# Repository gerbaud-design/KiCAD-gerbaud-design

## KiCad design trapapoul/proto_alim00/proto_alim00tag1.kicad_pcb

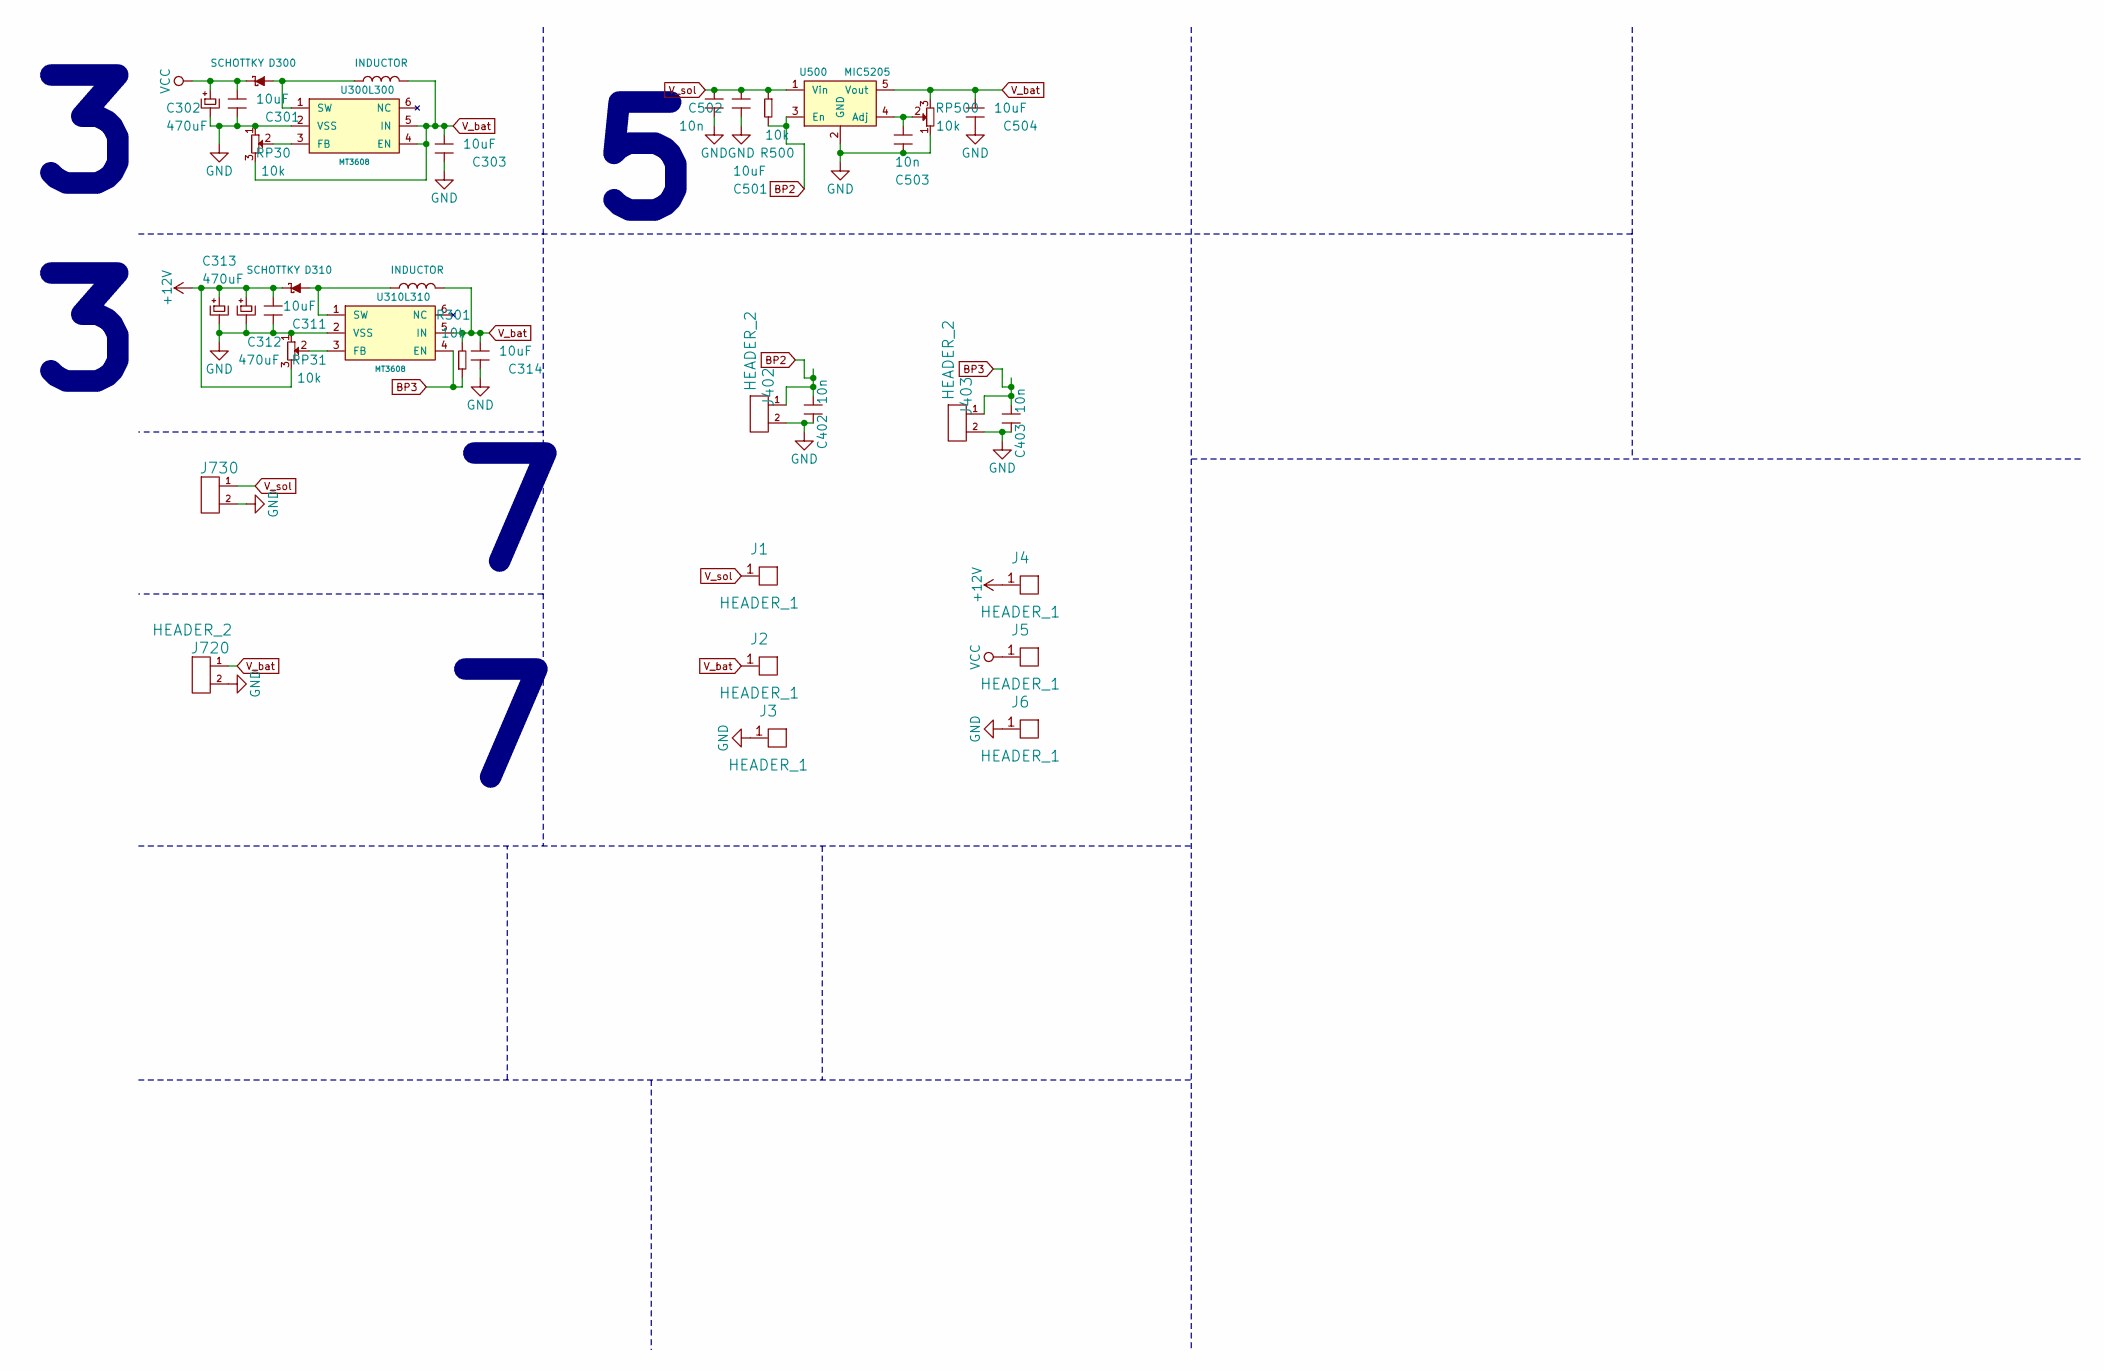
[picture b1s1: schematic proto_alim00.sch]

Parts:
C301, C303, C311, C314, C501, C504: 10uF; C_1206_HandSoldering
C302, C312, C313: 470uF; C_Radial_D8_L11.5_P3.5
C402, C403, C502, C503: 10n; C_1206_HandSoldering
D300, D310: SCHOTTKY; MiniMELF_Handsoldering
J1, J2, J3, J4, J5, J6: HEADER_1; Pin_Header_Straight_1x01
J402, J403, J720, J730: HEADER_2; Pin_Header_Straight_1x02
L300, L310: INDUCTOR; R_1206_HandSoldering
R301, R500: 10k; R_1206_HandSoldering
RP30, RP31, RP500: 10k; Potentiometer_Triwood_RM-065
U300, U310: MT3608; SOT-23-6_Handsoldering
U500: MIC5205; SOT-23-5_Handsoldering

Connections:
+12V: C311.1, C312.1, C313.1, D310.2 (K), J4.1, RP31.3
BP2: C402.1, J402.1, R500.2, U500.3 (En)
BP3: C403.1, J403.1, R301.1, U310.4 (EN)
GND: C301.2, C302.2, C303.2, C311.2, C312.2, C313.2, C314.2, C402.2, C403.2, C501.2, C502.2, C503.2, C504.2, J3.1, J6.1, J402.2, J403.2, J720.2, J730.2, RP30.1, RP31.1, RP500.1, U300.2 (VSS), U310.2 (VSS), U500.2 (GND)
unnamed: C503.1, RP500.2, U500.4 (Adj)
unnamed: D300.1 (A), L300.1, U300.1 (SW)
unnamed: D310.1 (A), L310.1, U310.1 (SW)
unnamed: RP30.2, U300.3 (FB)
unnamed: RP31.2, U310.3 (FB)
VCC: C301.1, C302.1, D300.2 (K), J5.1
V_bat: C303.1, C314.1, C504.1, J2.1, J720.1, L300.2, L310.2, R301.2, RP30.3, RP500.3, U300.4 (EN), U300.5 (IN), U310.5 (IN), U500.5 (Vout)
V_sol: C501.1, C502.1, J1.1, J730.1, R500.1, U500.1 (Vin)

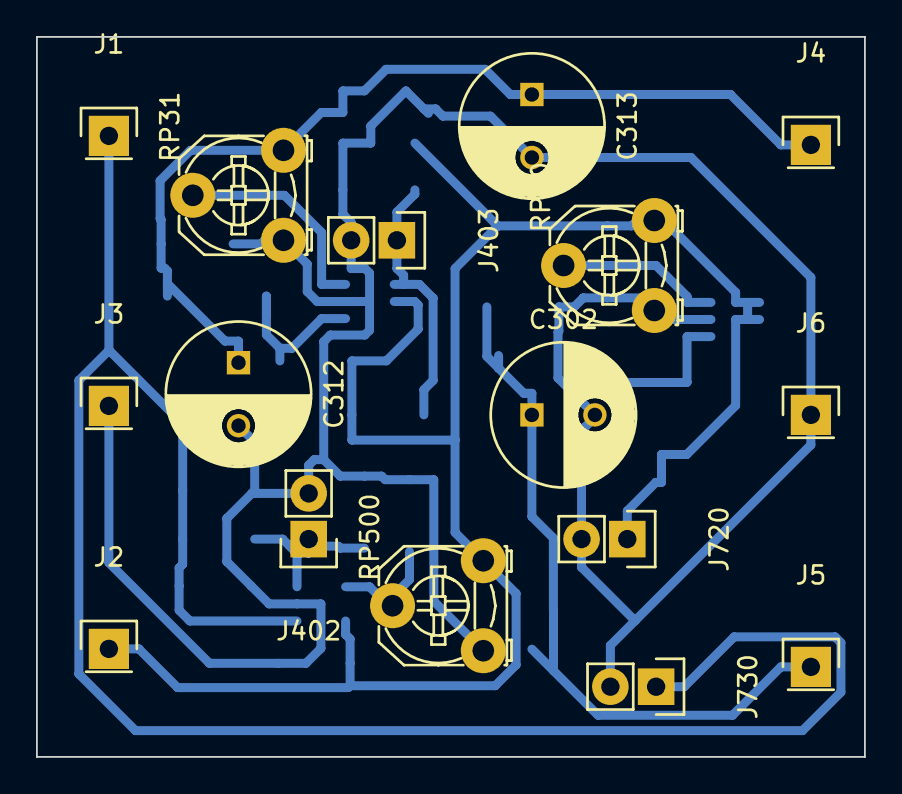
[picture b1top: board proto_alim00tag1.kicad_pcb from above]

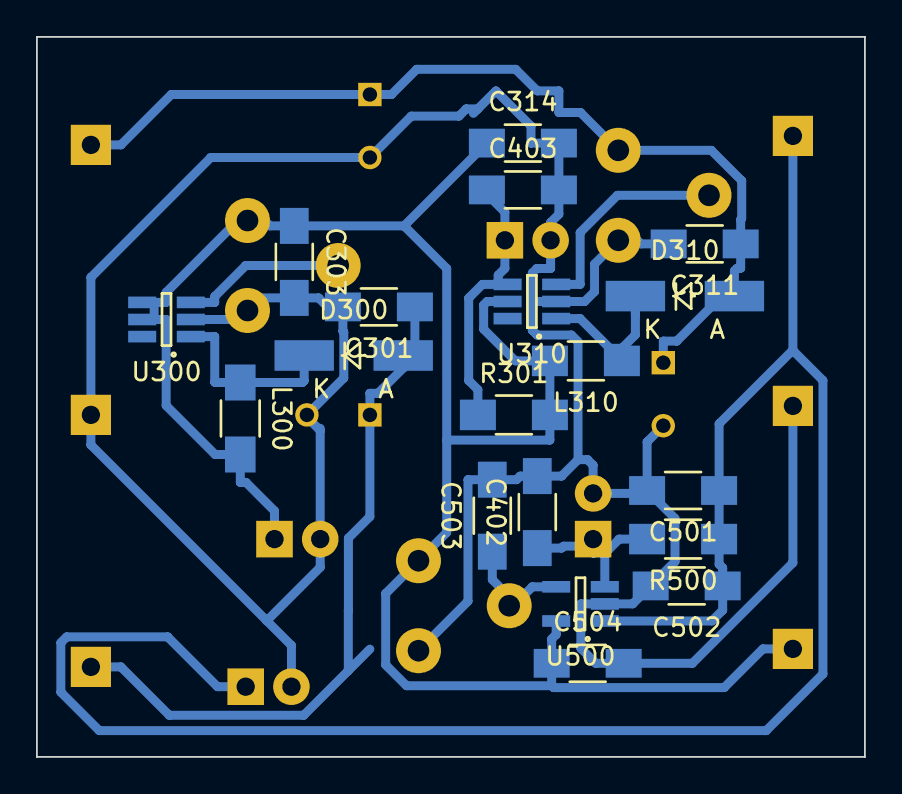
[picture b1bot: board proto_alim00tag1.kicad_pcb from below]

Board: 2 copper layers, 46.0 x 40.0 mm, 35 parts (19 on the bottom side), 12 nets.

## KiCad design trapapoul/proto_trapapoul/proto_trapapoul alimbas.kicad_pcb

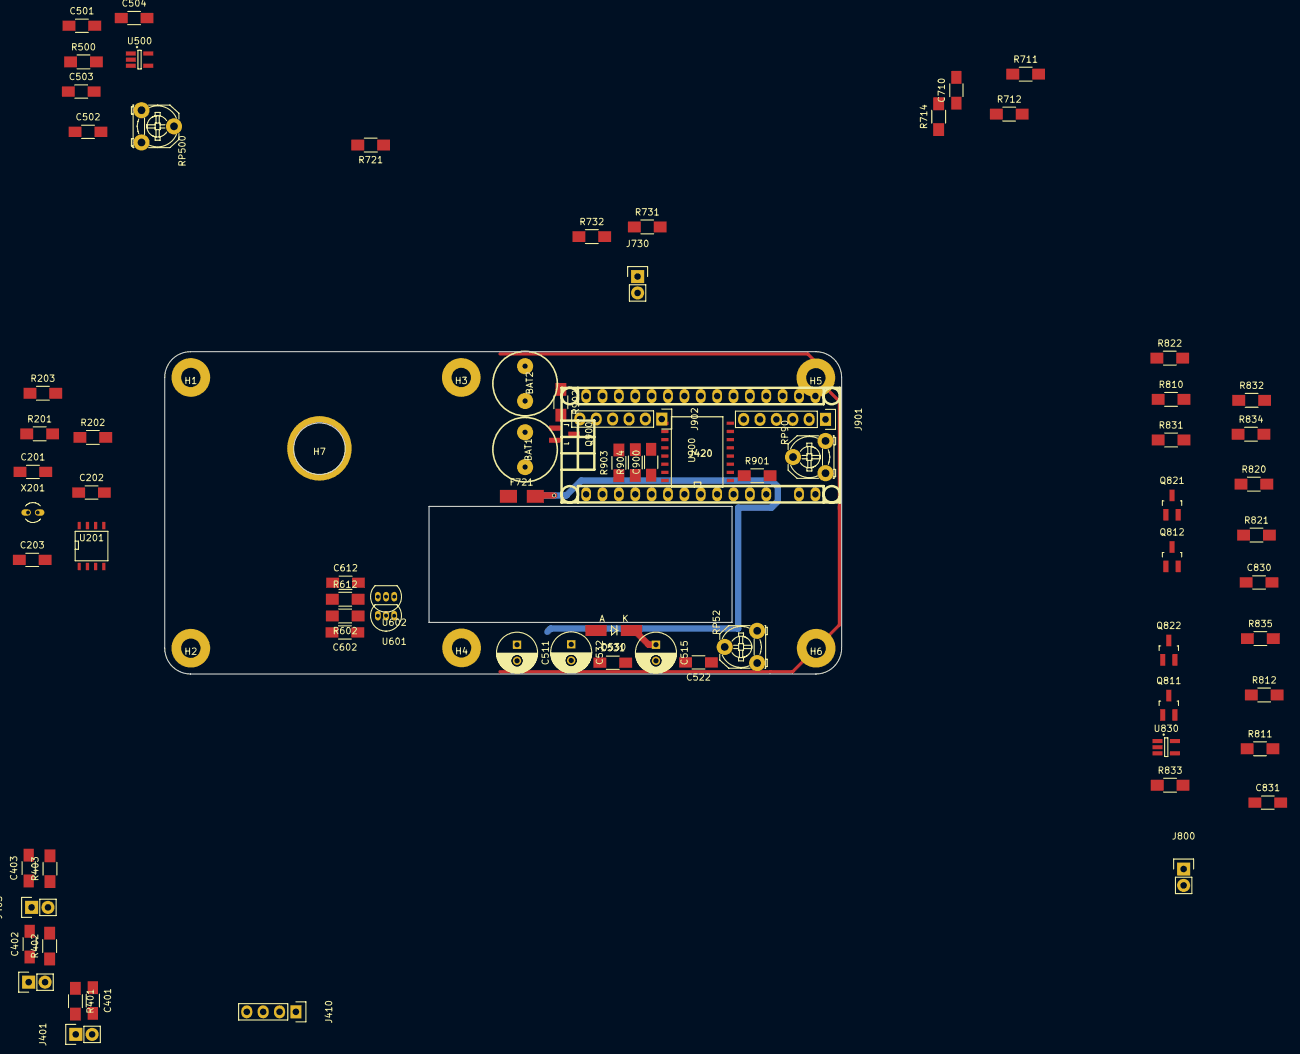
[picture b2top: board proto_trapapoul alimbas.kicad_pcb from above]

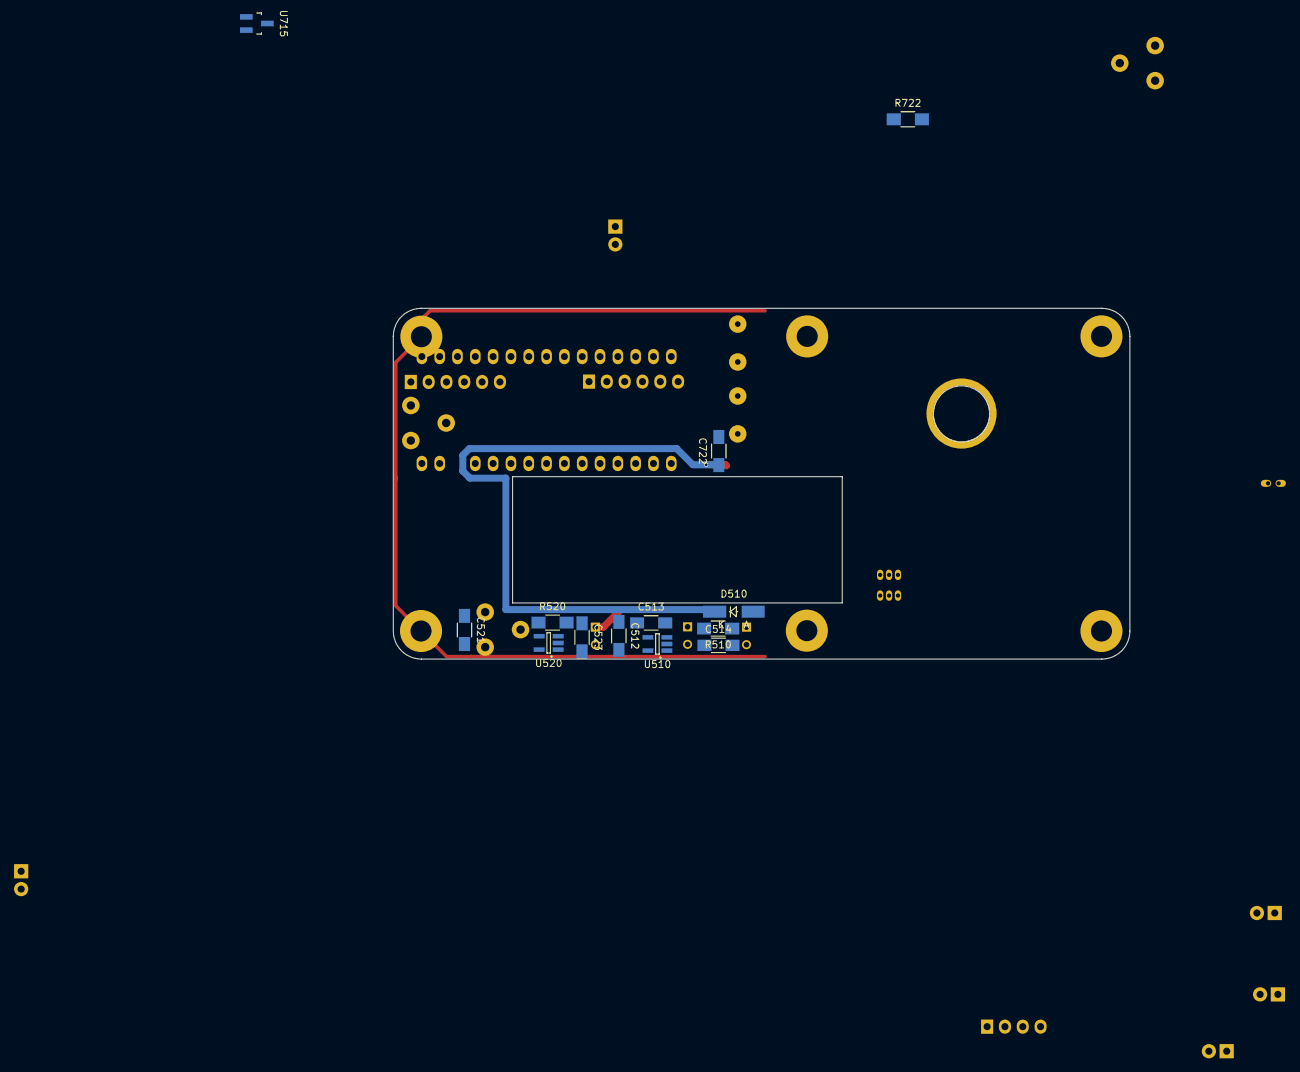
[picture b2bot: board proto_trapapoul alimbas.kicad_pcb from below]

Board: 2 copper layers, 105.0 x 50.0 mm, 99 parts (13 on the bottom side), 54 nets.

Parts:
BAT1, BAT2: BAT; HFC1025
C201, C202: 10p; C_1206_HandSoldering
C203, C401, C402, C403, C502, C503, C513, C522, C710: 10n; C_1206_HandSoldering
C501, C504, C512, C514, C521, C523, C531, C722: 10uF; C_1206_HandSoldering
C511, C515, C532: 470uF; C_Radial_D6.3_L11.2_P2.5
C602, C612, C900: 100nF; C_1206_HandSoldering
C830, C831: 100n; C_1206_HandSoldering
D510, D530: SCHOTTKY; MiniMELF_Handsoldering
F721: 5A; Fuse_SMD1206_HandSoldering
H1, H2, H3, H4, H5, H6: hole; 3mmPTH
H7: hole; MF85
J401, J402, J403, J730, J800: HEADER_2; Pin_Header_Straight_1x02
J410: HEADER_4; Pin_Header_Straight_1x04
J420: Arduino_Nano_Header; arduino_nano_header
J901, J902: HEADER_6; Pin_Header_Straight_1x06
Q811, Q821, Q900: PBSS4320; SOT-23_Handsoldering
Q812, Q822: PBSS5350; SOT-23_Handsoldering
R201, R401, R402, R403, R500, R510, R520, R711, R712, R714, R721, R722, R731, R732, R832, R901: 10k; R_1206_HandSoldering
R202, R203, R903, R904: 2.2k; R_1206_HandSoldering
R602, R612: 4k7; R_1206_HandSoldering
R810, R820: 3k3; R_1206_HandSoldering
R811, R812, R821, R822: 330; R_1206_HandSoldering
R831, R833, R834: 1k; R_1206_HandSoldering
R835: 0R2; R_1206_HandSoldering
R902: 4.7k; R_1206_HandSoldering
RP52, RP90, RP500: 10k; Potentiometer_Triwood_RM-065
U201: MCP7940; SOIC-8-N
U500, U510, U520: MIC5205; SOT-23-5_Handsoldering
U601, U602: A3144; TO-92_Inline_Narrow_Oval
U715: TLV431-DBZ; SOT-23_Handsoldering
U830: MCP601-SOT; SOT-23-5_Handsoldering
U900: PCF8574; SO-16-W
X201: 32.768K; Crystal_Round_Vertical_3mm_BigPad

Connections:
BP1: C401.1, J401.1, J420.2, R401.2
BP2: C402.1, J402.1, J420.6, R402.2
BP3: C403.1, J403.1, J420.1, R403.2
C_bkw: J420.8, R821.1
C_frw: J420.9, R811.2
GND: BAT2.2, C201.2, C202.2, C203.2, C401.2, C402.2, C403.2, C501.2, C502.2, C503.2, C504.2, C511.2, C512.2, C513.2, C514.2, C515.2, C521.2, C522.2, C523.2, C531.2, C532.2, C602.2, C612.1, C710.2, C722.2, C830.2, C831.2, C900.2, H1.1, H2.1, H3.1, H4.1, H5.1, H6.1, H7.1, J401.2, J402.2, J403.2, J410.1, J420.4, J420.29, J730.2, J901.1, Q900.2, R520.1, R711.2, R721.1, R732.2, R834.2, R835.1, RP52.1, RP90.1, RP500.1, U201.4, U500.2, U510.2, U520.2, U601.2, U602.2, U715.3, U830.2, U900.8
M_bat: J420.20, R721.2, R722.2
M_imot: C831.1, J420.19, R831.1
M_sol: J420.21, R731.1, R732.1
unnamed: BAT1.1, F721.1
unnamed: BAT1.2, BAT2.1
unnamed: C201.1, U201.2, X201.2
unnamed: C202.1, U201.1, X201.1
unnamed: C503.1, RP500.2, U500.4
unnamed: C511.1, C514.1, D510.2, R510.1, U510.1
unnamed: C513.1, U510.4
unnamed: C522.1, RP52.2, U520.4
unnamed: J901.3, RP90.2
unnamed: J901.4, U900.4
unnamed: J901.5, U900.5
unnamed: J901.6, U900.6
unnamed: J902.1, U900.9
unnamed: J902.2, U900.10
unnamed: J902.3, U900.11
unnamed: J902.4, U900.12
unnamed: J902.6, Q900.3
unnamed: Q811.1, R810.2, R811.1
unnamed: Q811.2, Q821.2, R810.1, R820.1, R833.2, R835.2
unnamed: Q812.1, R812.2
unnamed: Q821.1, R820.2, R821.2
unnamed: Q822.1, R822.2
unnamed: Q900.1, R902.2
unnamed: R510.2, U510.3
unnamed: R711.1, R712.2, U715.1
unnamed: R831.2, R832.1, U830.1
unnamed: R832.2, R834.1, U830.4
unnamed: R833.1, U830.3
unnamed: R901.1, U900.1, U900.2, U900.3
unnamed: R902.1, U900.7
SCL: J410.3, J420.24, R202.2, R904.2, U201.6, U900.14
SDA: J410.2, J420.23, R203.2, R903.2, U201.5, U900.15
VCC: C512.1, C515.1, C900.1, D530.1, J410.4, J420.27, J901.2, J902.5, R401.1, R402.1, R403.1, R602.2, R612.1, R901.2, R903.1, R904.1, RP90.3, U510.5, U900.16
VPP: C521.1, C830.1, Q812.2, Q822.2, R714.1, RP52.3, U520.5, U601.1, U602.1, U830.5
V_bat: C504.1, C523.1, C722.1, D510.1, F721.2, R722.1, RP500.3, U500.5, U520.1
V_ref: C710.1, J420.18, R712.1, R714.2, U715.2
V_rtc: C203.1, C531.1, C532.1, D530.2, R201.1, R202.1, R203.1, U201.8
V_sol: C501.1, C502.1, J730.1, R500.1, R731.2, U500.1
VppEn: J420.12, R520.2, U520.3
alarm: J420.5, R201.2, U201.3, U201.7
charge_OFF: J420.11, R500.2, U500.3
mot_A: J800.1, Q821.3, Q822.3, R812.1
mot_B: J800.2, Q811.3, Q812.3, R822.1
quadA: C602.1, J420.10, R602.1, U601.3
quadB: C612.2, J420.7, R612.2, U602.3
